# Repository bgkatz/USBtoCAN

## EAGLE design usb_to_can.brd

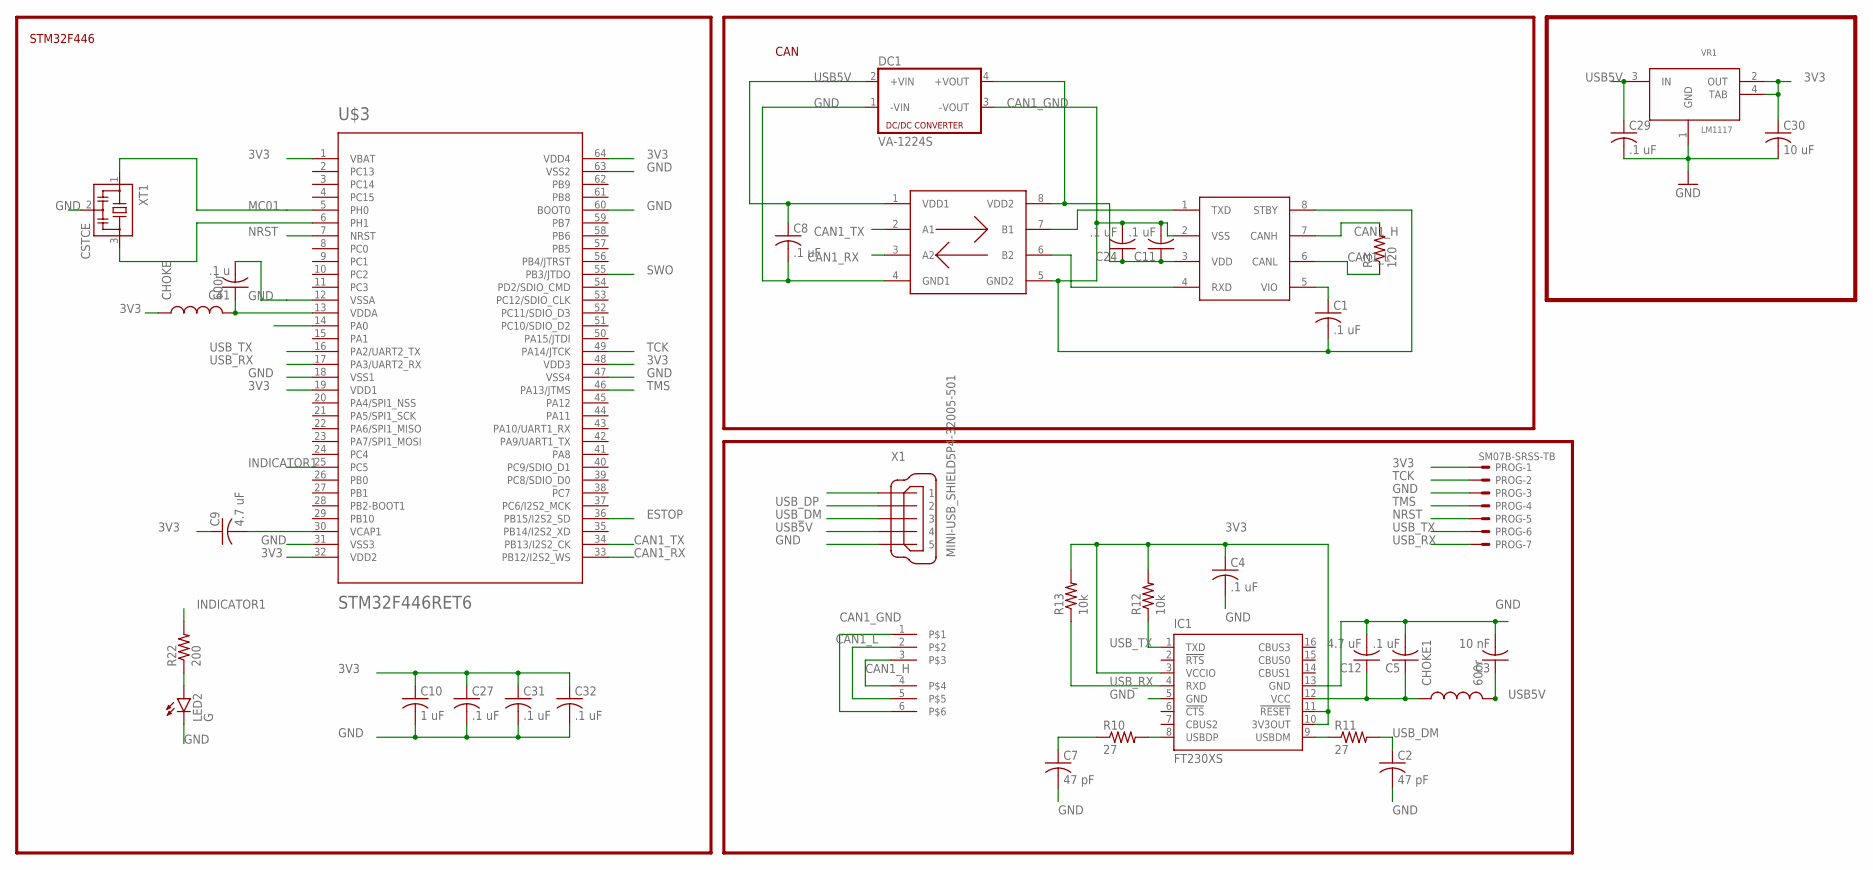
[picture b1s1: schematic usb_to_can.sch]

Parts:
C1, C4, C5, C8, C11, C24, C27, C29, C31, C32: .1 uF; C0402K
C2, C7: 47 pF; C0402K
C3: 10 nF; C0402K
C9, C12: 4.7 uF; C0402K
C10: 1 uF; C0402K
C30: 10 uF; C0402K
C41: .1 u; C0402K
CHOKE, CHOKE1: 600r; 0603
DC1: VA-1224S; 4SIL
IC1: FT230XS; SSOP16
LED2: G; LED-0603
PROG: SM07B-SRSS-TB
R3: 120; R0402
R10, R11: 27; R0402
R12, R13: 10k; R0402
R22: 200; R0402
U$1: 6-PIN; M80-5400642
U$3: STM32F446RET6; TQFP64
U$4: MCP2561; SO08
U$8: SI8410; SO08
VR1: LM1117; SOT-223
X1: MINI-USB_SHIELD5P4-32005-501; 32005-501
XT1: CSTCE

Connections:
3V3: C4.1, C9.1, C10.1, C27.1, C30.1, C31.1, C32.1, CHOKE.1, IC1.3 (VCCIO), IC1.10 (3V3OUT), IC1.11 (!RESET), PROG.1, R12.2, R13.2, U$3.1 (VBAT), U$3.19 (VDD1), U$3.32 (VDD2), U$3.48 (VDD3), U$3.64 (VDD4), VR1.2 (OUT), VR1.4 (TAB)
CAN1_GND: C1.2, C11.2, C24.2, DC1.3 (-VOUT), U$1.1, U$1.6, U$4.2 (VSS), U$4.8 (STBY), U$8.5 (GND2)
CAN1_H: R3.2, U$1.3, U$1.4, U$4.7 (CANH)
CAN1_L: R3.1, U$1.2, U$1.5, U$4.6 (CANL)
CAN1_RX: U$3.33 (PB12/I2S2_WS), U$8.3 (A2)
CAN1_TX: U$3.34 (PB13/I2S2_CK), U$8.2 (A1)
ESTOP: U$3.36 (PB15/I2S2_SD)
GND: C2.2, C3.2, C4.2, C5.2, C7.2, C8.2, C10.2, C12.2, C27.2, C29.2, C30.2, C31.2, C32.2, C41.2, DC1.1 (-VIN), IC1.5 (GND), IC1.13 (GND), LED2.C, PROG.3, U$3.12 (VSSA), U$3.18 (VSS1), U$3.31 (VSS3), U$3.47 (VSS4), U$3.60 (BOOT0), U$3.63 (VSS2), U$8.4 (GND1), VR1.1 (GND), X1.5, XT1.2
INDICATOR1: R22.2, U$3.25 (PC5)
MC01: U$3.5 (PH0), XT1.1
unnamed: C41.1, CHOKE.2, U$3.13 (VDDA)
unnamed: C9.2, U$3.30 (VCAP1)
unnamed: C1.1, U$4.5 (VIO)
unnamed: C5.1, C12.1, CHOKE1.1, IC1.12 (VCC)
unnamed: IC1.8 (USBDP), R10.2
unnamed: C11.1, C24.1, DC1.4 (+VOUT), U$4.3 (VDD), U$8.8 (VDD2)
unnamed: U$4.1 (TXD), U$8.7 (B1)
unnamed: IC1.9 (USBDM), R11.1
unnamed: U$4.4 (RXD), U$8.6 (B2)
unnamed: LED2.A, R22.1
unnamed: U$3.6 (PH1), XT1.3
NRST: PROG.5, U$3.7 (NRST)
SWO: U$3.55 (PB3/JTDO)
TCK: PROG.2, U$3.49 (PA14/JTCK)
TMS: PROG.4, U$3.46 (PA13/JTMS)
USB5V: C3.1, C8.1, C29.1, CHOKE1.2, DC1.2 (+VIN), U$8.1 (VDD1), VR1.3 (IN), X1.4
USB_DM: C2.1, R11.2, X1.3
USB_DP: C7.1, R10.1, X1.2
USB_RX: IC1.4 (RXD), PROG.7, R13.1, U$3.17 (PA3/UART2_RX)
USB_TX: IC1.1 (TXD), PROG.6, R12.1, U$3.16 (PA2/UART2_TX)

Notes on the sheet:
STM32F446
CAN

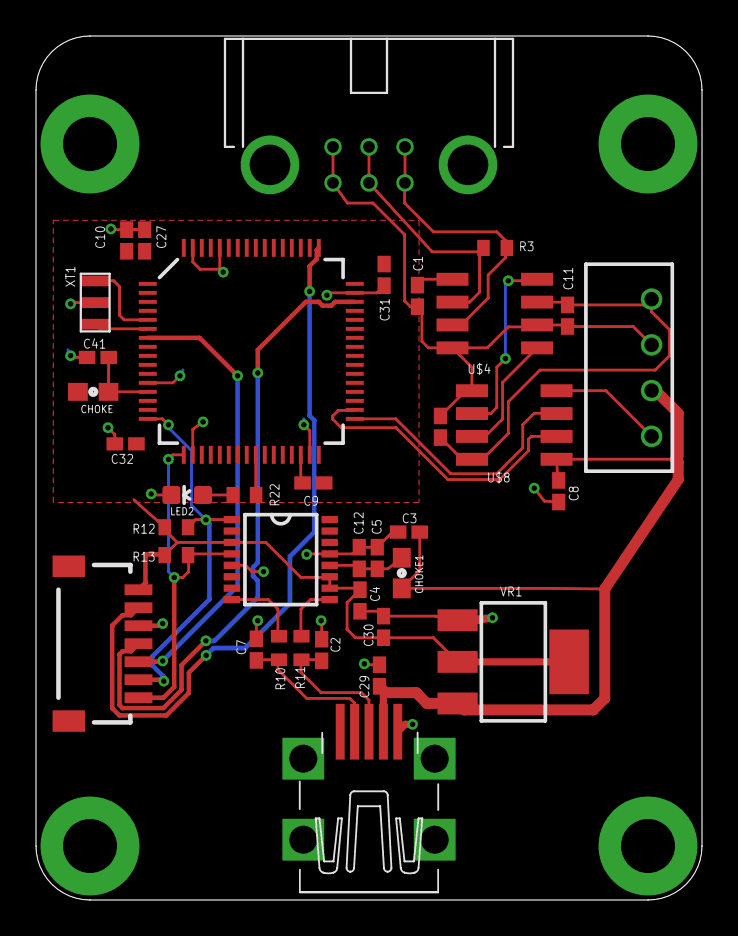
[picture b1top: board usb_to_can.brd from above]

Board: 2 copper layers, 37.0 x 48.0 mm, 37 parts (0 on the bottom side), 28 nets.

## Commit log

2019-08-08 committing files
2019-08-08 updated part values and BOM
2019-08-08 added python API
2019-08-08 added digikey cart link to bom

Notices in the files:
parts and their libraries:
SparkFun-Aesthetics: Licensing: Creative Commons ShareAlike 4.0 International - https://creativecommons.org/licenses/by-sa/4.0
